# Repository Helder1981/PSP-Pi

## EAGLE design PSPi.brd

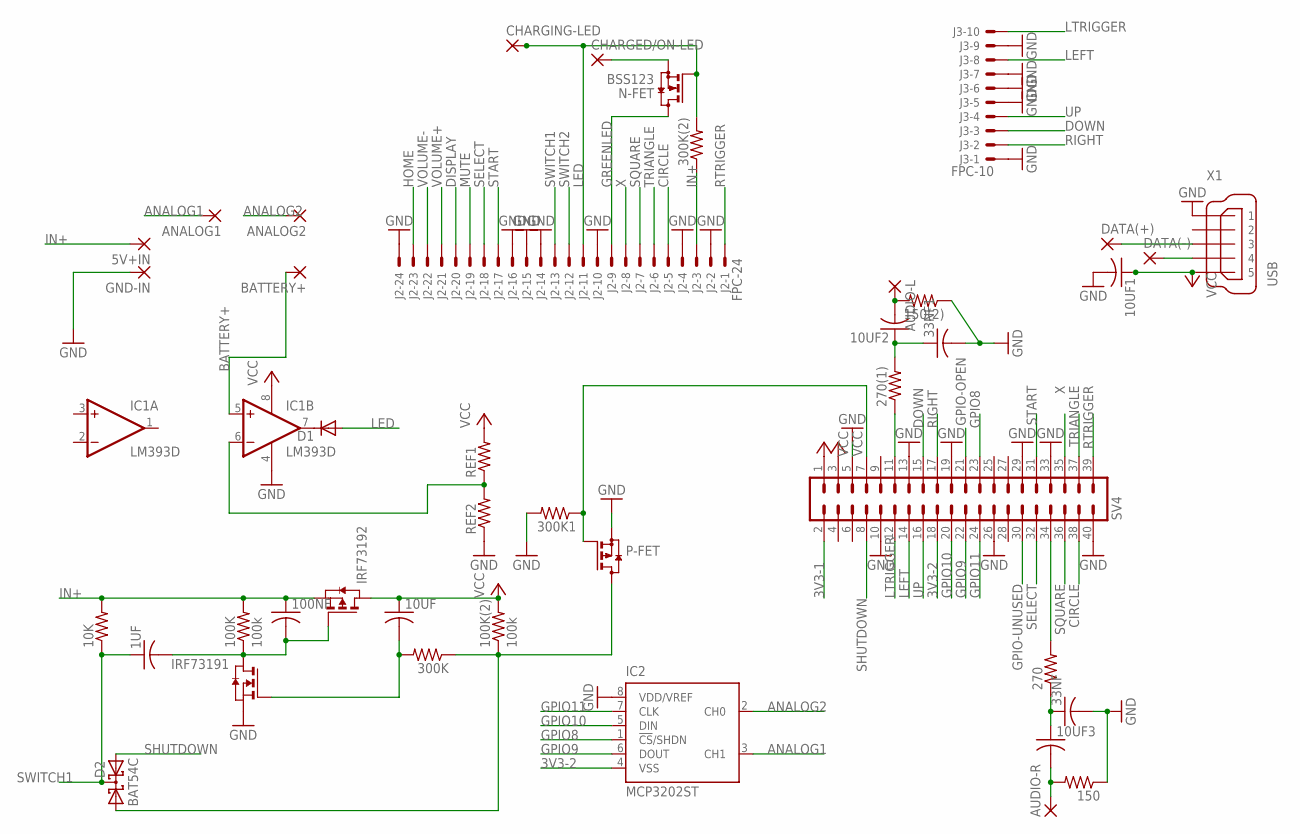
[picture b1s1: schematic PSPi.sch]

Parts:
1UF, 10UF, 10UF1, 10UF2, 10UF3, 33NF, 33NF1, 100NF: C-USC0805; C0805
5V+IN: SMD2; SMD1,27-2,54
10K, 150, 150(2), 270, 270(1), 300K, 300K1, 300K(2): R-US_R0805; R0805
100K, 100K(2): 100k; R0805
ANALOG1, ANALOG2: SMD2; SMD1,27-2,54
AUDIO-L: SMD2; SMD1,27-2,54
AUDIO-R: SMD2; SMD1,27-2,54
BATTERY+: SMD2; SMD1,27-2,54
CHARGED/ON-LED: SMD2; SMD1,27-2,54
CHARGING-LED: SMD2; SMD1,27-2,54
D1: DIODE-SOD323-R; SOD323-R
D2: BAT54C; SOT23
DATA(+): SMD2; SMD1,27-2,54
DATA(-): SMD2; SMD1,27-2,54
GND-IN: SMD2; SMD1,27-2,54
IC1: LM393D; SO08
IC2: MCP3202ST; TSSOP8
IRF7319: PN_MOSFET-SO8; SO8
J2: FPC-24; XF2R-2415-4A
J3: FPC-10; XF2L-1035-1
N-FET: BSS123; SOT23
P-FET: BSS84; SOT23
REF1, REF2: R-US_R0805; R0805
SV4: MA20-2
X1: USB; 32005-201

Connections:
3V3-1: SV4.2
3V3-2: IC2.4 (VSS), SV4.18
ANALOG1: ANALOG1.1, IC2.3 (CH1)
ANALOG2: ANALOG2.1, IC2.2 (CH0)
BATTERY+: BATTERY+.1, IC1.5 (+IN)
CIRCLE: J2.5 (MS), SV4.38
DISPLAY: J2.20 (MS)
DOWN: J3.3 (MS), SV4.15
GND: 10UF1.2, 33NF.2, 33NF1.2, 150.1, 150(2).1, 300K1.2, GND-IN.1, IC1.4 (V-), IC2.8 (VDD/VREF), IRF7319.1 (S), J2.2 (MS), J2.4 (MS), J2.10 (MS), J2.14 (MS), J2.15 (MS), J2.16 (MS), J2.24 (MS), J3.1 (MSV), J3.5 (MS), J3.6 (MS), J3.7 (MS), J3.9 (MS), P-FET.2 (S), REF2.1, SV4.5, SV4.10, SV4.13, SV4.19, SV4.26, SV4.29, SV4.33, SV4.40, X1.1
GPIO8: IC2.1 (!CS!/SHDN), SV4.23
GPIO9: IC2.6 (DOUT), SV4.22
GPIO10: IC2.5 (DIN), SV4.20
GPIO11: IC2.7 (CLK), SV4.24
GPIO-OPEN: SV4.21
GPIO-UNUSED: SV4.30
GREENLED: J2.9 (MS), N-FET.3 (D)
HOME: J2.23 (MS)
IN+: 5V+IN.1, 10K.2, 100K.2, 100NF.1, 300K(2).1, IRF7319.3 (S), J2.3 (MS)
LED: 300K(2).2, CHARGING-LED.1, D1.A, J2.11 (MS), N-FET.1 (G)
LEFT: J3.8 (MS), SV4.14
LTRIGGER: J3.10 (MS), SV4.12
MUTE: J2.19 (MS)
unnamed: IC1.6 (-IN), REF1.1, REF2.2
unnamed: D1.C, IC1.7 (OUT)
unnamed: 1UF.2, 100K.1, 100NF.2, IRF7319.4 (G), IRF7319.7 (D), IRF7319.8 (D)
unnamed: DATA(-).1, X1.4
unnamed: 10UF.2, 300K.2, IRF7319.2 (G)
unnamed: 100K(2).1, 300K.1, D2.1 (A1), P-FET.3 (D)
unnamed: 300K1.1, P-FET.1 (G), SV4.7
unnamed: 10UF3.1, 33NF.1, 270.1
unnamed: CHARGED/ON-LED.1, N-FET.2 (S)
unnamed: DATA(+).1, X1.3
unnamed: 10UF2.1, 33NF1.1, 270(1).2
unnamed: 10UF3.2, 150.2, AUDIO-R.1
unnamed: 270.2, SV4.34
unnamed: 270(1).1, SV4.11
unnamed: 10UF2.2, 150(2).2, AUDIO-L.1
RIGHT: J3.2 (MS), SV4.17
RTRIGGER: J2.1 (MSV), SV4.39
SELECT: J2.18 (MS), SV4.32
SHUTDOWN: D2.2 (A2), SV4.8
SQUARE: J2.7 (MS), SV4.36
START: J2.17 (MS), SV4.31
SWITCH1: 1UF.1, 10K.1, D2.3 (CC), J2.13 (MS)
SWITCH2: J2.12 (MS)
TRIANGLE: J2.6 (MS), SV4.37
UP: J3.4 (MS), SV4.16
VCC: 10UF.1, 10UF1.1, 100K(2).2, IC1.8 (V+), IRF7319.5 (D), IRF7319.6 (D), REF1.2, SV4.1, SV4.3, X1.5
VOLUME+: J2.21 (MS)
VOLUME-: J2.22 (MS)
X: J2.8 (MS), SV4.35

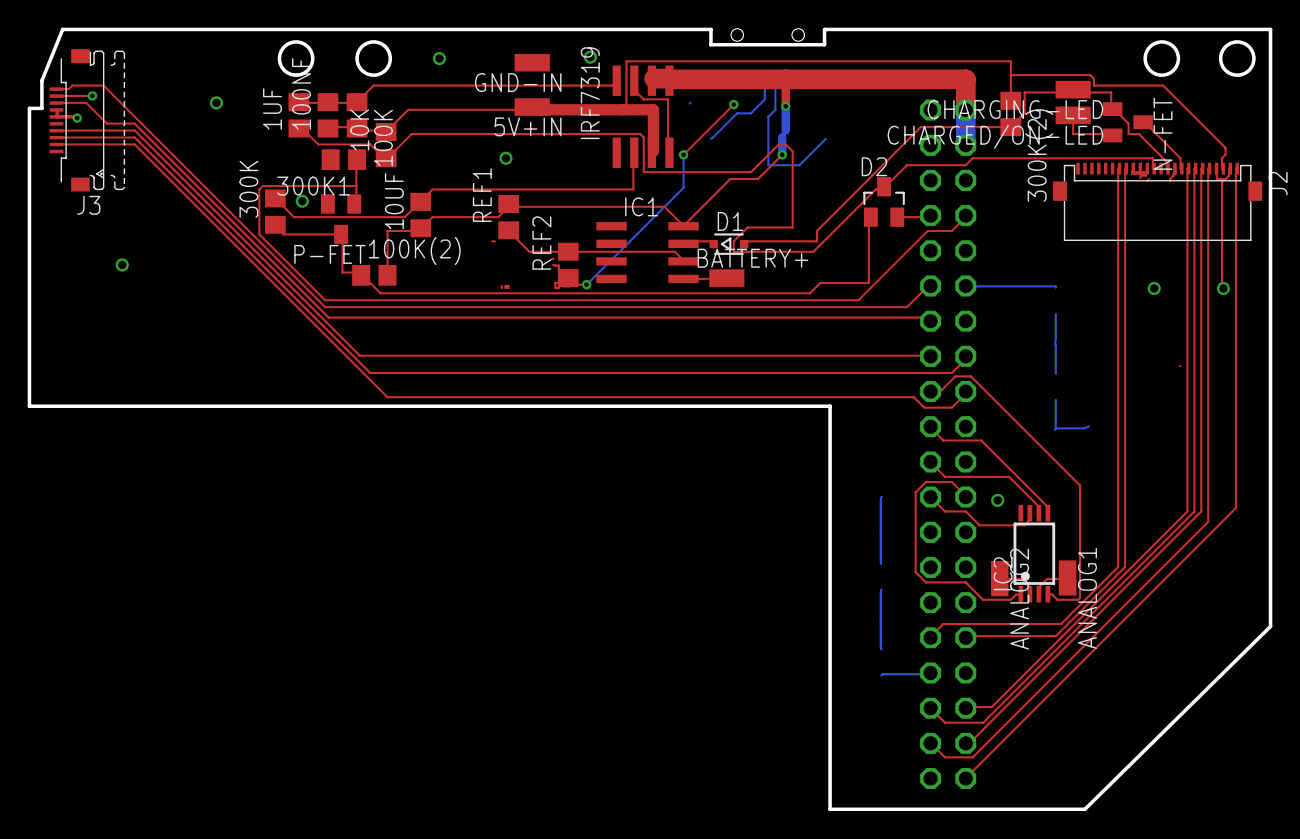
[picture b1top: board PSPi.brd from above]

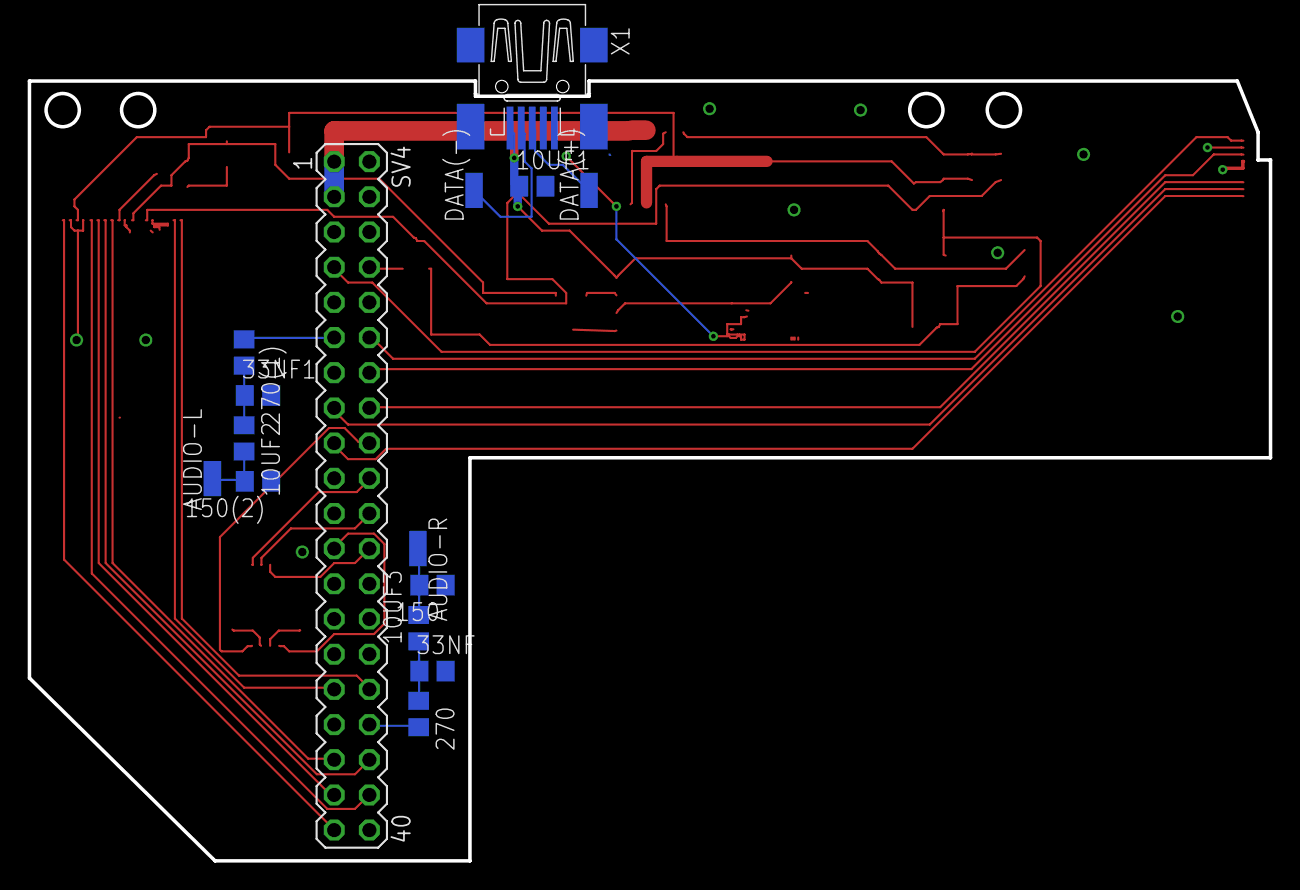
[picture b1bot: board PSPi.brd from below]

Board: 2 copper layers, 89.6 x 56.3 mm, 42 parts (15 on the bottom side), 42 nets.

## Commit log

2016-10-03 ReadMe.MD
    This is a Project started by OtherMod to mod a PSP with a Pi Zero to play emulators.
2016-10-03 Added Initial Eagle Files
